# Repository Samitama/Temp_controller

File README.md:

# Temperature Controller With Arduino

This project temperature controller Fan

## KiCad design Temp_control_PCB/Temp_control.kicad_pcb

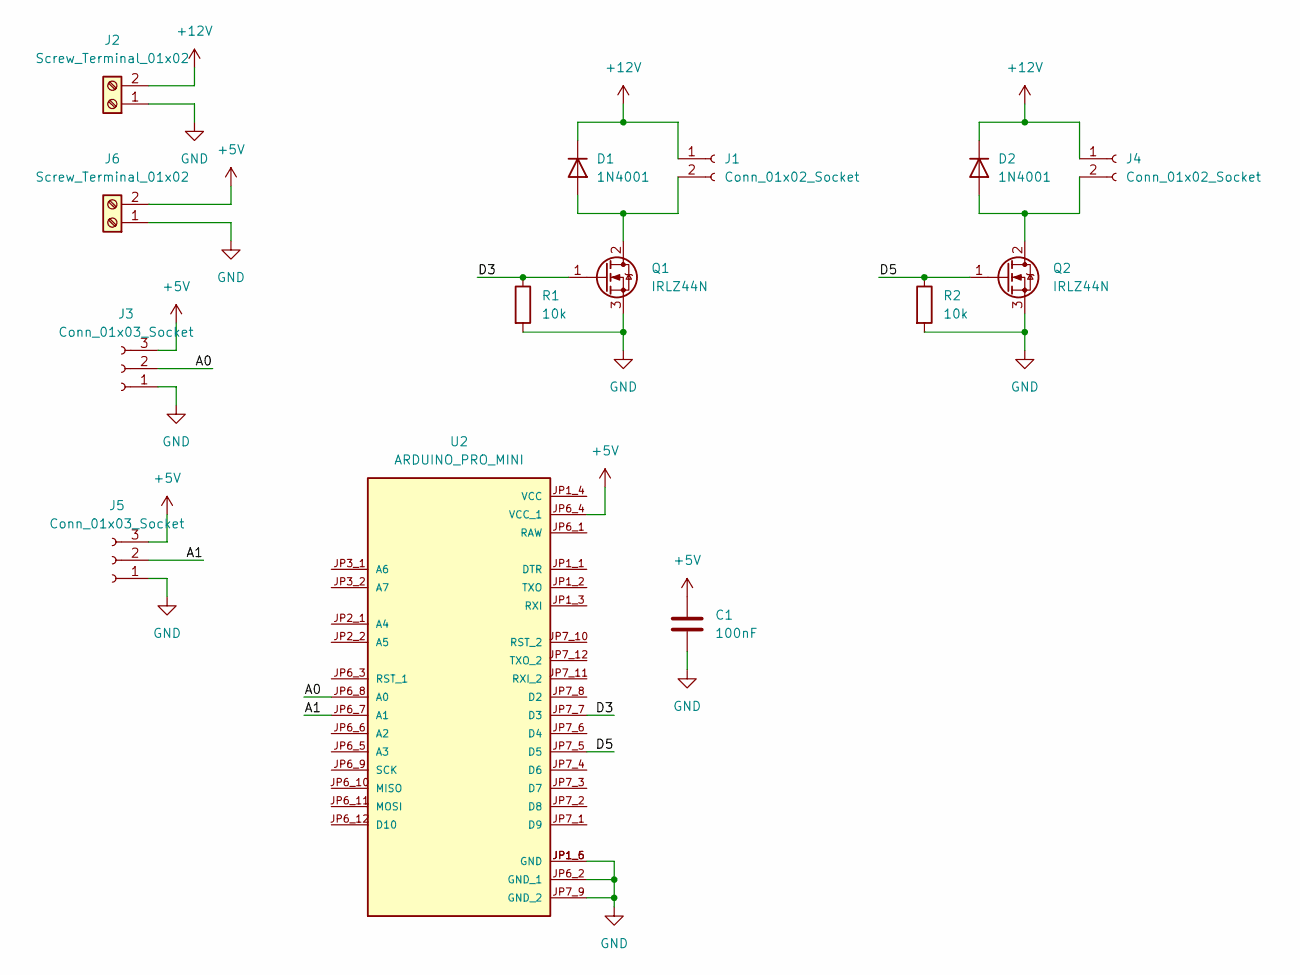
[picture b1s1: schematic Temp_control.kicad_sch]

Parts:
C1: 100nF
D1, D2: 1N4001; D_DO-41_SOD81_P10.16mm_Horizontal
J1, J4: Conn_01x02_Socket; PinSocket_1x02_P2.54mm_Vertical
J2, J6: Screw_Terminal_01x02; TerminalBlock_Altech_AK300-2_P5.00mm
J3, J5: Conn_01x03_Socket; PinSocket_1x03_P2.54mm_Vertical
Q1, Q2: IRLZ44N; TO-220-3_Vertical
R1, R2: 10k; R_Axial_DIN0204_L3.6mm_D1.6mm_P7.62mm_Horizontal
U2: ARDUINO_PRO_MINI; MODULE_ARDUINO_PRO_MINI; PARTREV N/A

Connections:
+5V: C1.1, J3.3, J5.3, J6.2, U2.JP6_4 (VCC_1)
+12V: D1.1 (K), D2.1 (K), J1.1, J2.2, J4.1
/A0: J3.2, U2.JP6_8 (A0)
/A1: J5.2, U2.JP6_7 (A1)
/D3: Q1.1 (G), R1.1, U2.JP7_7 (D3)
/D5: Q2.1 (G), R2.1, U2.JP7_5 (D5)
GND: C1.2, J2.1, J3.1, J5.1, J6.1, Q1.3 (S), Q2.3 (S), R1.2, R2.2, U2.JP1_5 (GND), U2.JP1_6 (GND), U2.JP6_2 (GND_1), U2.JP7_9 (GND_2)
unnamed: D1.2 (A), J1.2, Q1.2 (D)
unnamed: D2.2 (A), J4.2, Q2.2 (D)

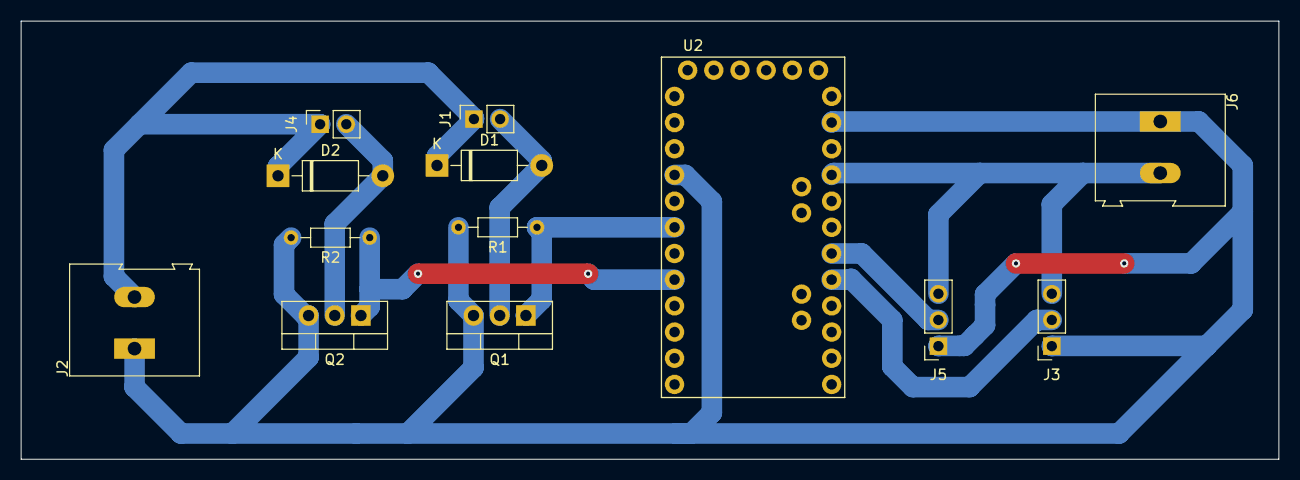
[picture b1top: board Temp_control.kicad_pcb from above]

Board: 2 copper layers, 122.0 x 42.5 mm, 13 parts (0 on the bottom side), 9 nets.

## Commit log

2022-07-25 text-file
2022-07-25 Readme.md
2022-07-25 add develop
2022-07-28 1.hafta
2022-07-28 main
2023-02-05 temp_controller
2023-04-05 temp_controller_fan
    this file tempature control with arduino
